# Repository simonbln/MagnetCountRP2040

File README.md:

# MagnetCountRP2040
A battery-powered, universal pulse counter using an RP2040 and Hall effect sensor. Displays real-time data on an OLED screen.

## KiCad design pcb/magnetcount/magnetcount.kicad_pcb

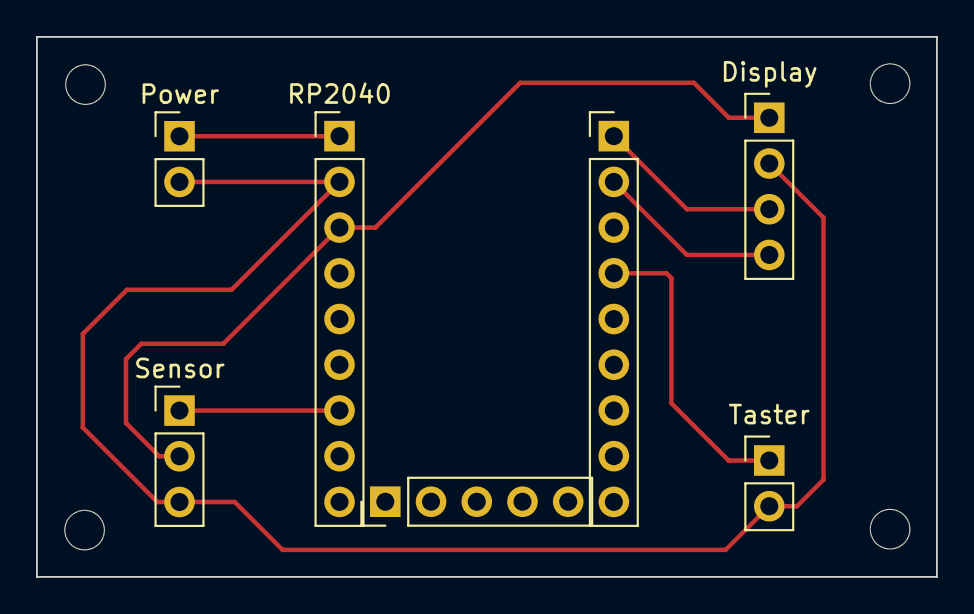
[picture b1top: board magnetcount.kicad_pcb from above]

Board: 2 copper layers, 50.0 x 30.0 mm, 7 parts (0 on the bottom side), 7 nets.

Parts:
Display: Conn_01x04_Female; PinHeader_1x04_P2.54mm_Vertical
J2: Conn_01x05_Female; PinHeader_1x05_P2.54mm_Vertical
J3: Conn_01x09_Female; PinHeader_1x09_P2.54mm_Vertical
Power: Conn_01x02_Female; PinHeader_1x02_P2.54mm_Vertical
RP2040: Conn_01x09_Female; PinHeader_1x09_P2.54mm_Vertical
Sensor: Conn_01x03_Female; PinHeader_1x03_P2.54mm_Vertical
Taster: Conn_01x02_Female; PinHeader_1x02_P2.54mm_Vertical

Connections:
unnamed: Power.1, RP2040.1
unnamed: Display.3, J3.1
unnamed: Display.4, J3.2
unnamed: J3.4, Taster.1
unnamed: RP2040.7, Sensor.1
unnamed: Display.1, RP2040.3, Sensor.2
unnamed: Display.2, Power.2, RP2040.2, Sensor.3, Taster.2

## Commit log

2026-04-30 progress
